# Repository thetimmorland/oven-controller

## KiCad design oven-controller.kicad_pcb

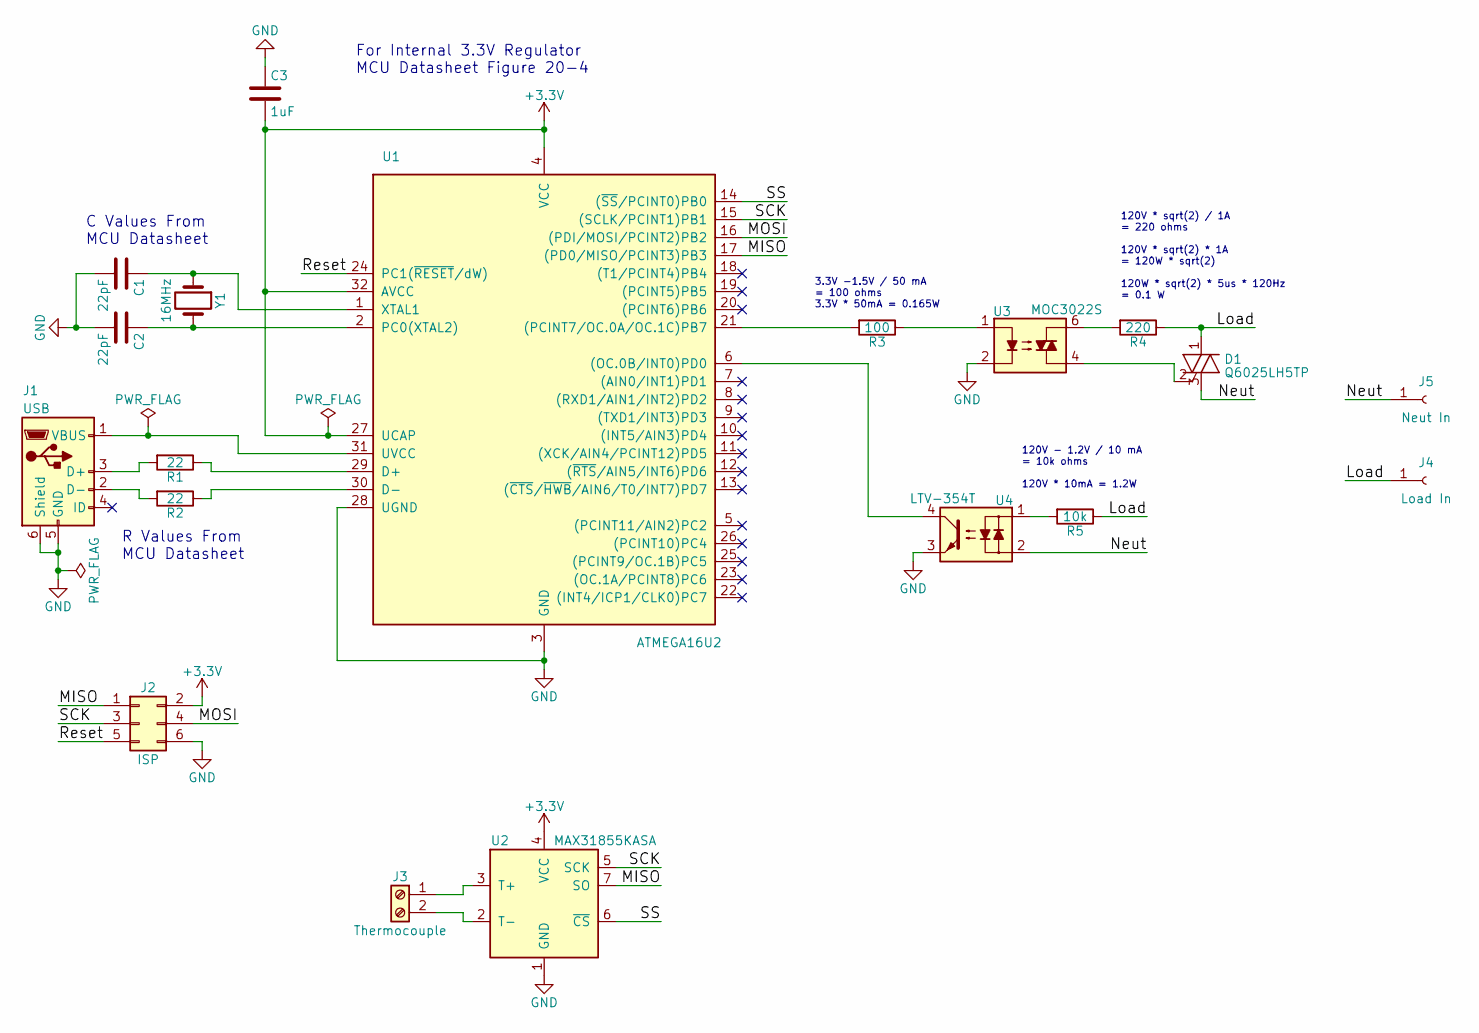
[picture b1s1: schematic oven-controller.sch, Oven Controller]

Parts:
C1, C2: 22pF; C_0805_HandSoldering
C3: 1uF; C_0805_HandSoldering
D1: Q6025LH5TP; TO-220-3_Vertical_Heatsink
J1: USB; USB_Micro-B_Molex_47346-0001
J2: ISP; Pin_Header_Straight_2x03_Pitch2.54mm
J3: Thermocouple; TerminalBlock_Phoenix_MPT-2.54mm_2pol
J4: Load In; SolderWirePad_single_2mmDrill
J5: Neut In; SolderWirePad_single_2mmDrill
R1, R2: 22; R_0805_HandSoldering
R3: 100; R_0805_HandSoldering
R4: 220; R_2512_HandSoldering
R5: 10k; R_Axial_DIN0614_L14.3mm_D5.7mm_P15.24mm_Horizontal
U1: ATMEGA16U2; TQFP-32_7x7mm_Pitch0.8mm
U2: MAX31855KASA; MAX-90-0096
U3: MOC3022S; MOC302X
U4: LTV-354T
Y1: 16MHz; Crystal_HC49-U_Vertical

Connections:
+3V3: C3.2, J2.2, U1.4 (VCC), U1.27 (UCAP), U1.32 (AVCC), U2.4 (VCC)
/Load: D1.1 (A1), J4.1, R4.1, R5.1
/MISO: J2.1, U1.17 ((PD0/MISO/PCINT3)PB3), U2.7 (SO)
/MOSI: J2.4, U1.16 ((PDI/MOSI/PCINT2)PB2)
/Neut: D1.3 (A2), J5.1, U4.2
/Reset: J2.5, U1.24 (PC1(~RESET~/dW))
/SCK: J2.3, U1.15 ((SCLK/PCINT1)PB1), U2.5 (SCK)
/SS: U1.14 ((~SS~/PCINT0)PB0), U2.6 (~CS~)
GND: C1.2, C2.2, C3.1, J1.5 (GND), J1.6 (Shield), J2.6, U1.3 (GND), U1.28 (UGND), U2.1 (GND), U3.2, U4.3
unnamed: C1.1, U1.1 (XTAL1), Y1.1
unnamed: C2.1, U1.2 (PC0(XTAL2)), Y1.2
unnamed: D1.2 (G), U3.4
unnamed: J1.1 (VBUS), U1.31 (UVCC)
unnamed: J1.2 (D-), R2.2
unnamed: J1.3 (D+), R1.2
unnamed: J3.1, U2.3 (T+)
unnamed: J3.2, U2.2 (T-)
unnamed: R1.1, U1.29 (D+)
unnamed: R2.1, U1.30 (D-)
unnamed: R3.1, U3.1
unnamed: R3.2, U1.21 ((PCINT7/OC.0A/OC.1C)PB7)
unnamed: R4.2, U3.6
unnamed: R5.2, U4.1
unnamed: U1.6 ((OC.0B/INT0)PD0), U4.4

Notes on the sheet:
For Internal 3.3V Regulator MCU Datasheet Figure 20-4
C Values From MCU Datasheet
R Values From MCU Datasheet
3.3V -1.5V / 50 mA = 100 ohms 3.3V * 50mA = 0.165W
120V - 1.2V / 10 mA = 10k ohms 120V * 10mA = 1.2W
120V * sqrt(2) / 1A = 220 ohms 120V * sqrt(2) * 1A = 120W * sqrt(2) 120W * sqrt(2) * 5us * 120Hz = 0.1 W

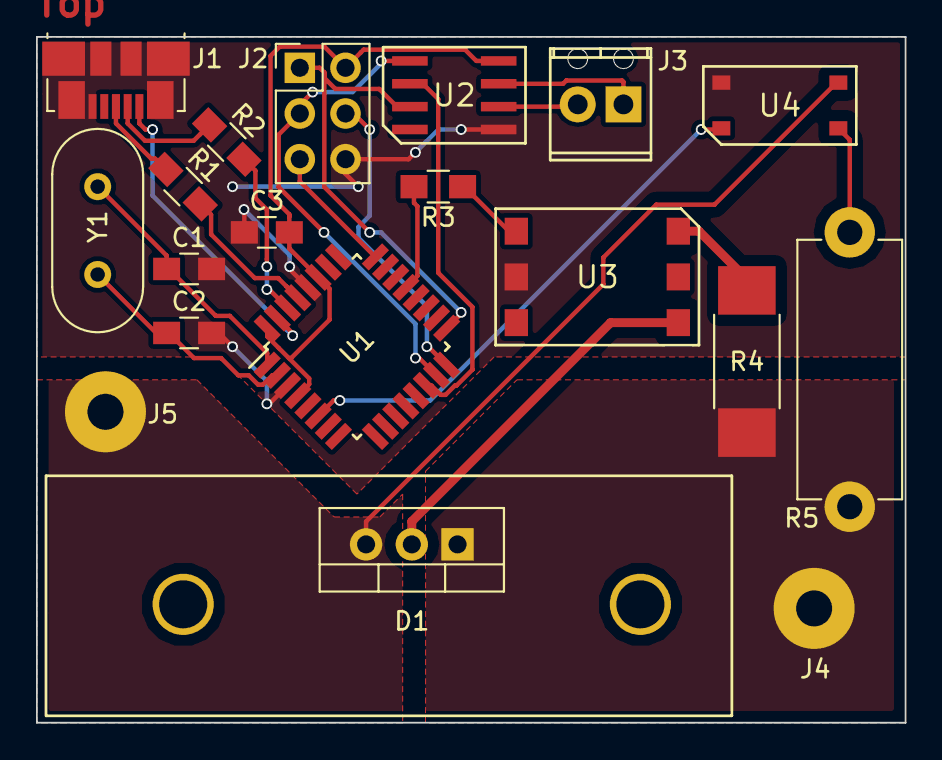
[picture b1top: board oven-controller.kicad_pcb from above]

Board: 2 copper layers, 48.3 x 38.1 mm, 19 parts (0 on the bottom side), 24 nets.

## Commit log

2018-02-26 Added kicad files
2018-03-10 Wrote program to generate lookup table
2018-03-14 oven-controller v2
